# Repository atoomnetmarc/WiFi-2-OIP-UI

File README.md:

# Status

Unfinished. Untested.

# What?

This is a **WiFi-connected display with LEDs** that gives new life to a reclaimed display board from an obsolete [Octalarm-IP](https://www.adesys.nl/en/product-octalarm-ip-adesys2).

The project consists of:

- A custom PCB that hosts an **ESP32-S2** microcontroller with WiFi connectivity
- A **128x64 LCD display** (Crystal Clear Technology G64128S18YBW00 with NT7534 controller)
- **20 red and 20 green LEDs** for status indication
- **Backlight control** for the LCD

The ESP32-S2 controls the display and LEDs via SPI.

# BOM

See: [Kicad/bom/ibom.html](Kicad/bom/ibom.html)

## BOM remarks

U1 should be a 5V buck converter in the footprint of a TO-220. It should be capable of outputting 5V at 1A. Input voltage should be greater than 12V.

J201 are 2 pieces of 1x05 2.54mm pp low profile (7.5mm) pin header instead of a Micro-MaTch connector.

For connecting TP203 you need 2cm of red wire.

The ESP32-S2 should come with 2 pieces of 2x08 2.54mm pin headers. Discard them and order 4 pieces of 1x08 2.54mm pp low profile (7.5mm) pin headers.

J201 Phoenix contact 1803277+1851999 can also be 1803277+1803578.

# Soldering and assembly instructions

Solder the pin headers on the ESP32-S2, use some old IDC connectors to perfectly align the headers. Like this:

Solder F1, D1. Solder U1 (the buck converter) laying flat (PCBs are now on the same plane). Cut pins (6 cuts) of U1 flush with PCB. Solder J2, C1 and C2. Cut pins of J2 flush with PCB. Solder one end of the red wire to TP203 on the bottom. The right side of the PCB now look like this:

Set your lab power supply to 12V CV, 0.25A CC. Then connect 12V to J2. Observe less than 10mA current. Measure 5V between TP203 and ground. Disconnect power supply.

Passed? Now solder A1 (the ESP32-S2 module). Do you not use low profile pin headers? Then cut pins flush with PCB. Works best before soldering.

Connect power supply again. Observe about 10mA current if ESP32-S2 is new and empty or about 40mA when flashed with firmware. Disconnect power supply.

Desolder the J201 MicroMatch 1.27mm socket from the display board.

Gently clean the PCB and the ESP32-S2 if you want.

Connect this PCB to the back of the display board using 2 pieces of low profile 1x5 2.54mm pin headers in the J201 footprints of both PCBs. The hole J202 on both PCB should almost align. But do not solder the header yet.
First solder a 1x02 2.54mm pin header on J202 of both PCBs to keep PCBs separated. Now solder the J201 pin header.

Solder the red wire onto the TP203 pad of the display board.

Connect power supply again. Observe about 20mA current (or 50mA when flashed). Disconnect power supply.

Make sure none of the pins (ESP32-S2, U1, J2) of this PCB touch display board:

# Firmware

Flash the firmware of the ESP32-S2. The firmware of the ATmega48 MCU of the display board is embedded in the ESP32-S2 firmware and will be flashed by the ESP32-S2.

# 3D-printed stand

You could 3d-print [a stand](3d/WiFi-2-OIP-UI%20stand.stl) for this contraption.

# Display board

Information about the display board.

## Pinout J201

| #   | name          | remarks    | ESP32 pin |
| --- | ------------- | ---------- | --------- |
| 1   | GND           |            |
| 2   | V+            | unused     |
| 3   | MCU reset     |            | IO5       |
| 4   | MCU interrupt | active low | IO1       |
| 5   | LCD RS        |            | IO4       |
| 6   | SPI clock     |            | IO7       |
| 7   | SPI MISO      |            | IO9       |
| 8   | SPI MOSI      |            | IO11      |
| 9   | SPI SS LCD    | active low | IO14      |
| 10  | SPI SS MCU    | active low | IO12      |

## LCD

LCD is a 128x64 Crystal Clear Technology [G64128S18YBW00](https://www.arrow.com/en/products/g64128s18ybw00/crystal-clear-technology-sdn-bhd). It contains a [Novatek NT7534](https://www.crystalfontz.com/controllers/Novatek/NT7534/) controller.

When testing with [U8g2](https://github.com/olikraus/u8g2) using U8G2_ST7565_ERC12864_ALT results in a working LCD.

## MCU

The MCU is a TQFP-32 [Atmega48](https://www.microchip.com/en-us/product/atmega48) that is responsible for driving the 20 red and 20 green LEDs and the backlight of the LCD.

## Testpoints

| #     | name          | remarks  |
| ----- | ------------- | -------- |
| TP201 | MCU PD1       | not used |
| TP202 | V+            | not used |
| TP203 | 5V            |
| TP204 | 3.3V          |
| TP205 | MCU PC5, PC6  | not used |
| TP206 | SPI clock     |
| TP207 | SPI MISO      |
| TP208 | SPI MOSI      |
| TP209 | MCU SS        |
| TP210 | MCU reset     |
| TP211 | MCU interrupt |
| TP212 | 5V            |
| TP213 | GND           |
| TP214 | 3.3V          |
| TP301 |               | not used |
| TP302 |               | not used |
| TP303 |               | not used |
| TP304 |               | not used |
| TP305 |               | not used |
| TP306 |               | not used |
| TP307 |               | not used |
| TP308 |               | not used |
| TP309 |               | not used |
| TP310 |               | not used |
| TP402 | LCD reset     |
| TP404 | LCD SS        |
| TP405 | LCD RS        |
| TP501 |               | not used |
| TP502 |               | not used |
| TP503 | MCU ADC7      | not used |
| TP504 | MCU PB1       | not used |
| TP506 |               | not used |
| TP507 |               | not used |
| TP508 |               | not used |

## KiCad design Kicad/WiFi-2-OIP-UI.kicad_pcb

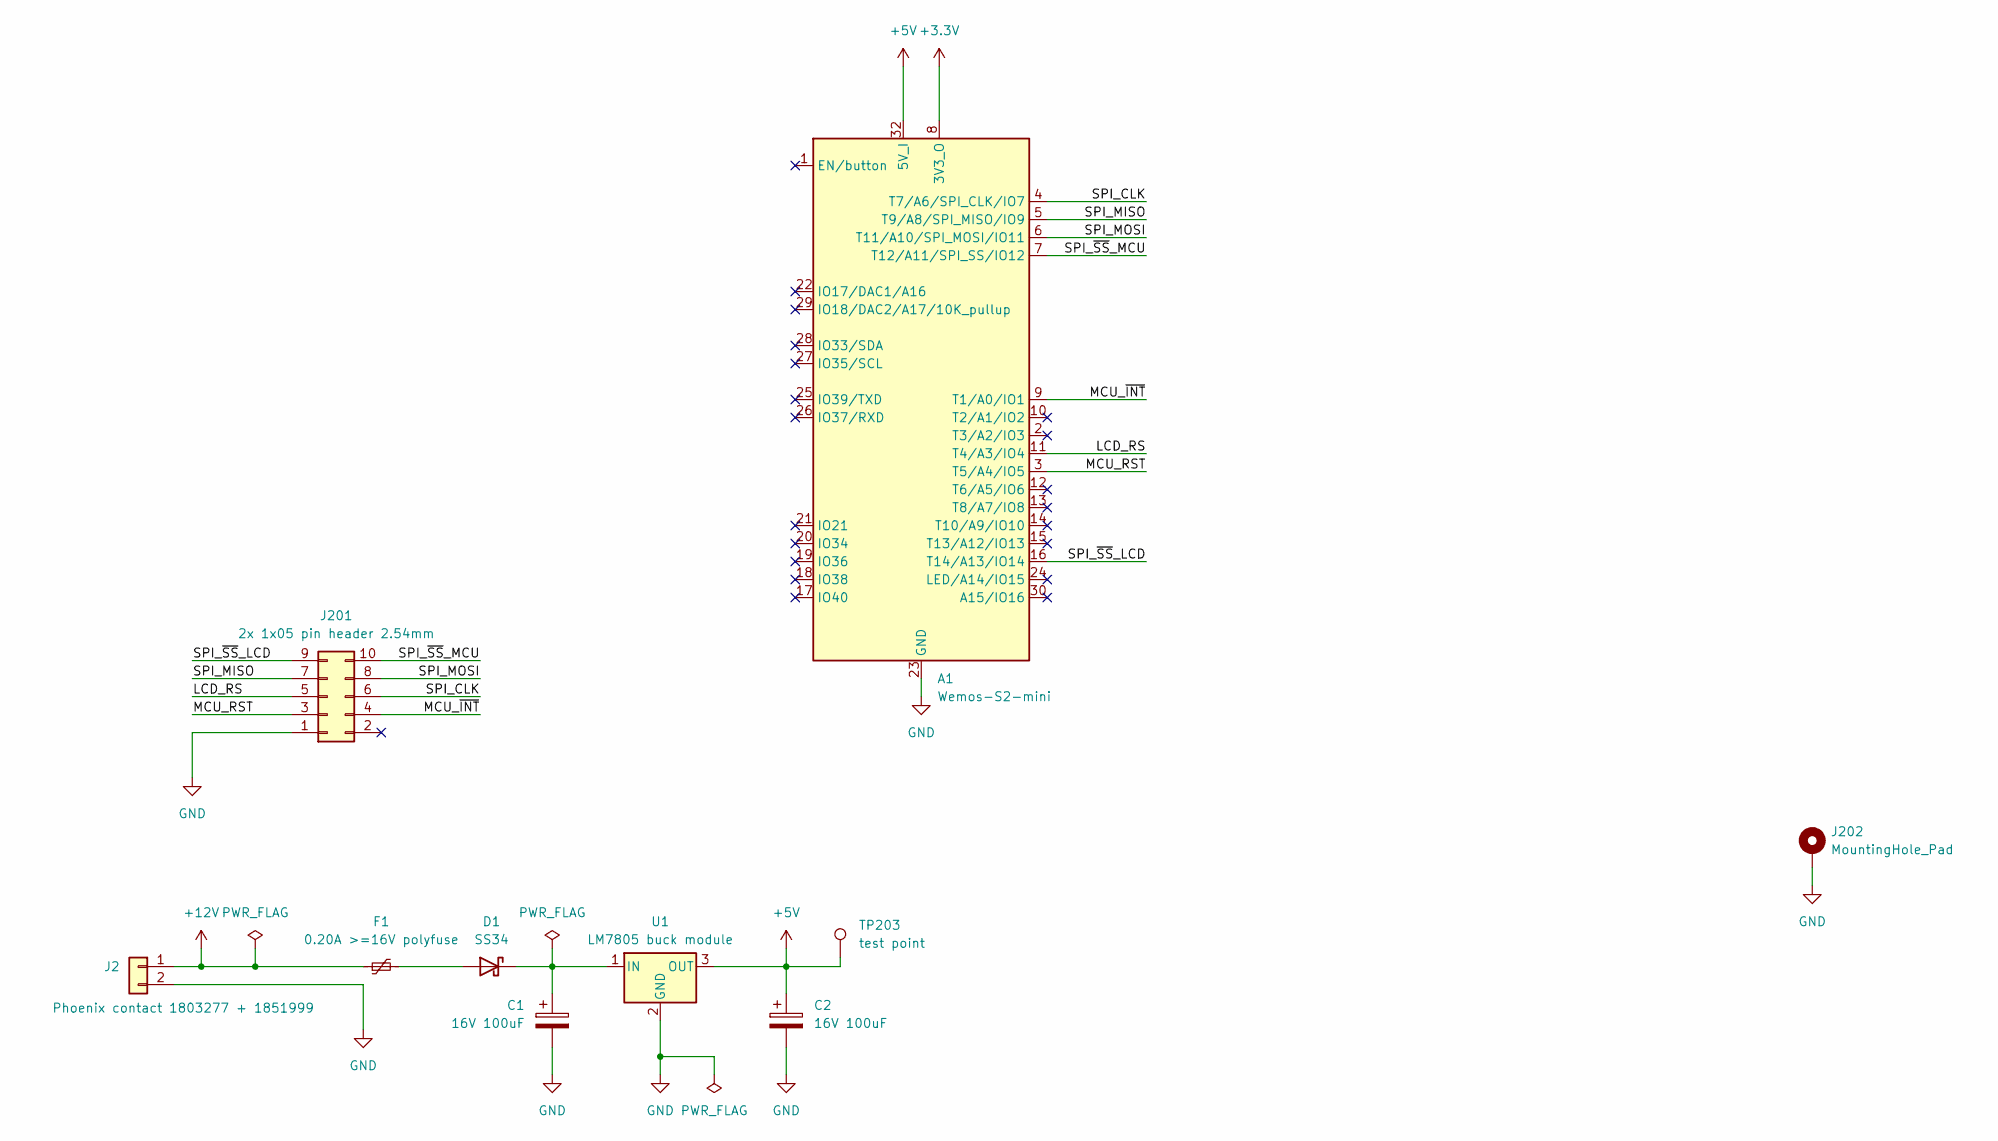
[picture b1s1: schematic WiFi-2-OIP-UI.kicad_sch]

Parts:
A1: Wemos-S2-mini
C1, C2: 16V 100uF; CP_Radial_D5.0mm_P2.00mm
D1: SS34; D_SMA
F1: 0.20A >=16V polyfuse; Fuse_1206_3216Metric_Pad1.42x1.75mm_HandSolder
J2: Phoenix contact 1803277 + 1851999; PhoenixContact_MC_1,5_2-G-3.5_1x02_P3.50mm_Horizontal
J201: 2x 1x05 pin header 2.54mm; TE_Micro-MaTch_1-215079-0_2x05_P1.27mm_Vertical
J202: MountingHole_Pad; MountingHole_4.5mm_Pad_Via
TP203: TestPoint; TestPoint_THTPad_2.5x2.5mm_Drill1.2mm
U1: LM7805 buck module; TO-220-3_Vertical

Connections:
+3.3V: A1.8 (3V3_O)
+5V: A1.32 (5V_I), C2.1, TP203.1, U1.3 (OUT)
+12V: F1.1, J2.1
/LCD_RS: A1.11 (T4/A3/IO4), J201.5
/MCU_RST: A1.3 (T5/A4/IO5), J201.3
/MCU_~INT: A1.9 (T1/A0/IO1), J201.4
/SPI_CLK: A1.4 (T7/A6/SPI_CLK/IO7), J201.6
/SPI_MISO: A1.5 (T9/A8/SPI_MISO/IO9), J201.7
/SPI_MOSI: A1.6 (T11/A10/SPI_MOSI/IO11), J201.8
/SPI_~SS_LCD: A1.16 (T14/A13/IO14), J201.9
/SPI_~SS_MCU: A1.7 (T12/A11/SPI_SS/IO12), J201.10
GND: A1.23 (GND), A1.31 (GND), C1.2, C2.2, J2.2, J201.1, J202.1, U1.2 (GND)
unnamed: D1.2 (A), F1.2
unnamed: C1.1, D1.1 (K), U1.1 (IN)

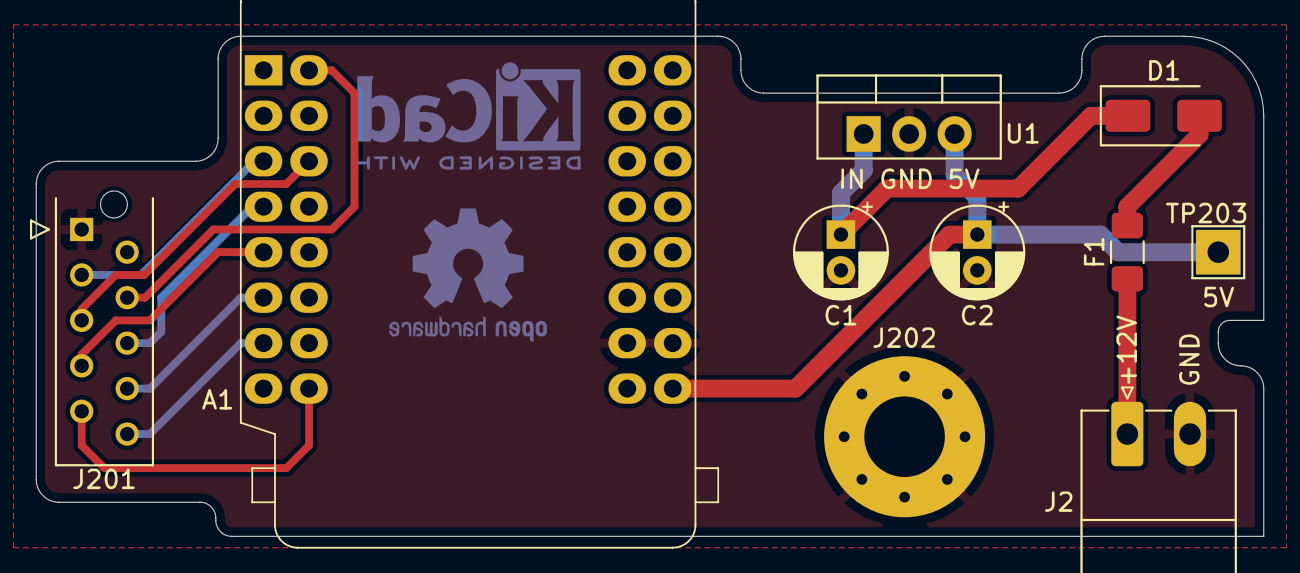
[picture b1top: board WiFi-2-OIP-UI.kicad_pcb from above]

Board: 2 copper layers, 68.6 x 27.9 mm, 10 parts (0 on the bottom side), 13 nets.

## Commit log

2024-05-11 Initial commit.
2024-05-23 Add soldering and assembly instructions.
2024-05-24 Add MCU code to control LEDs.
2024-05-24 Add documentation about display board.
2024-05-24 Add U8g2 working lcd model.
2024-05-25 Add 3d-printable stand.
2024-05-25 Pics or did not happen.
2024-06-10 Change fuse to 0.2A
2024-06-10 Soldered a few pcbs, made changes to instructions.
2025-03-30 Reformat extra_scripts.
2025-03-30 Bump atmelavr platform.
2025-03-30 Create proof-of-concept code for esp32.
2025-04-01 Update Copyright year of MCU and shared project.
2025-04-01 Tweak instruction id's.
2025-04-06 Things start working.
2025-04-06 Add rudimentary 2nd wifi credentials support.
2026-01-23 Add CONTRIBUTING.md
2026-02-06 Update libs.
2026-02-07 Erase evidence of MQTT over Websockets.
2026-02-07 Update Copyright year.
2026-02-07 Improve README.md.

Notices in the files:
Kicad/WiFi-2-OIP-UI.kicad_pcb:
Apache License, Version 2.0
README.md:
License: Apache 2.0
